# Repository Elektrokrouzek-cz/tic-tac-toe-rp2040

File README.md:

# Tic-tac-toe based on RP2040
This is the construction of tic-tac-toe game based on Raspberry Pi Pico (RP2040). It consists of 3x3 game layout with Neopixel 5mm LEDs and buttons.

Code is written in Micropython

PCB is 2-layer and was designed using KiCad 9. Fabrication output for JLCPCB is in gerber folder.

**Happy coldering and coding**

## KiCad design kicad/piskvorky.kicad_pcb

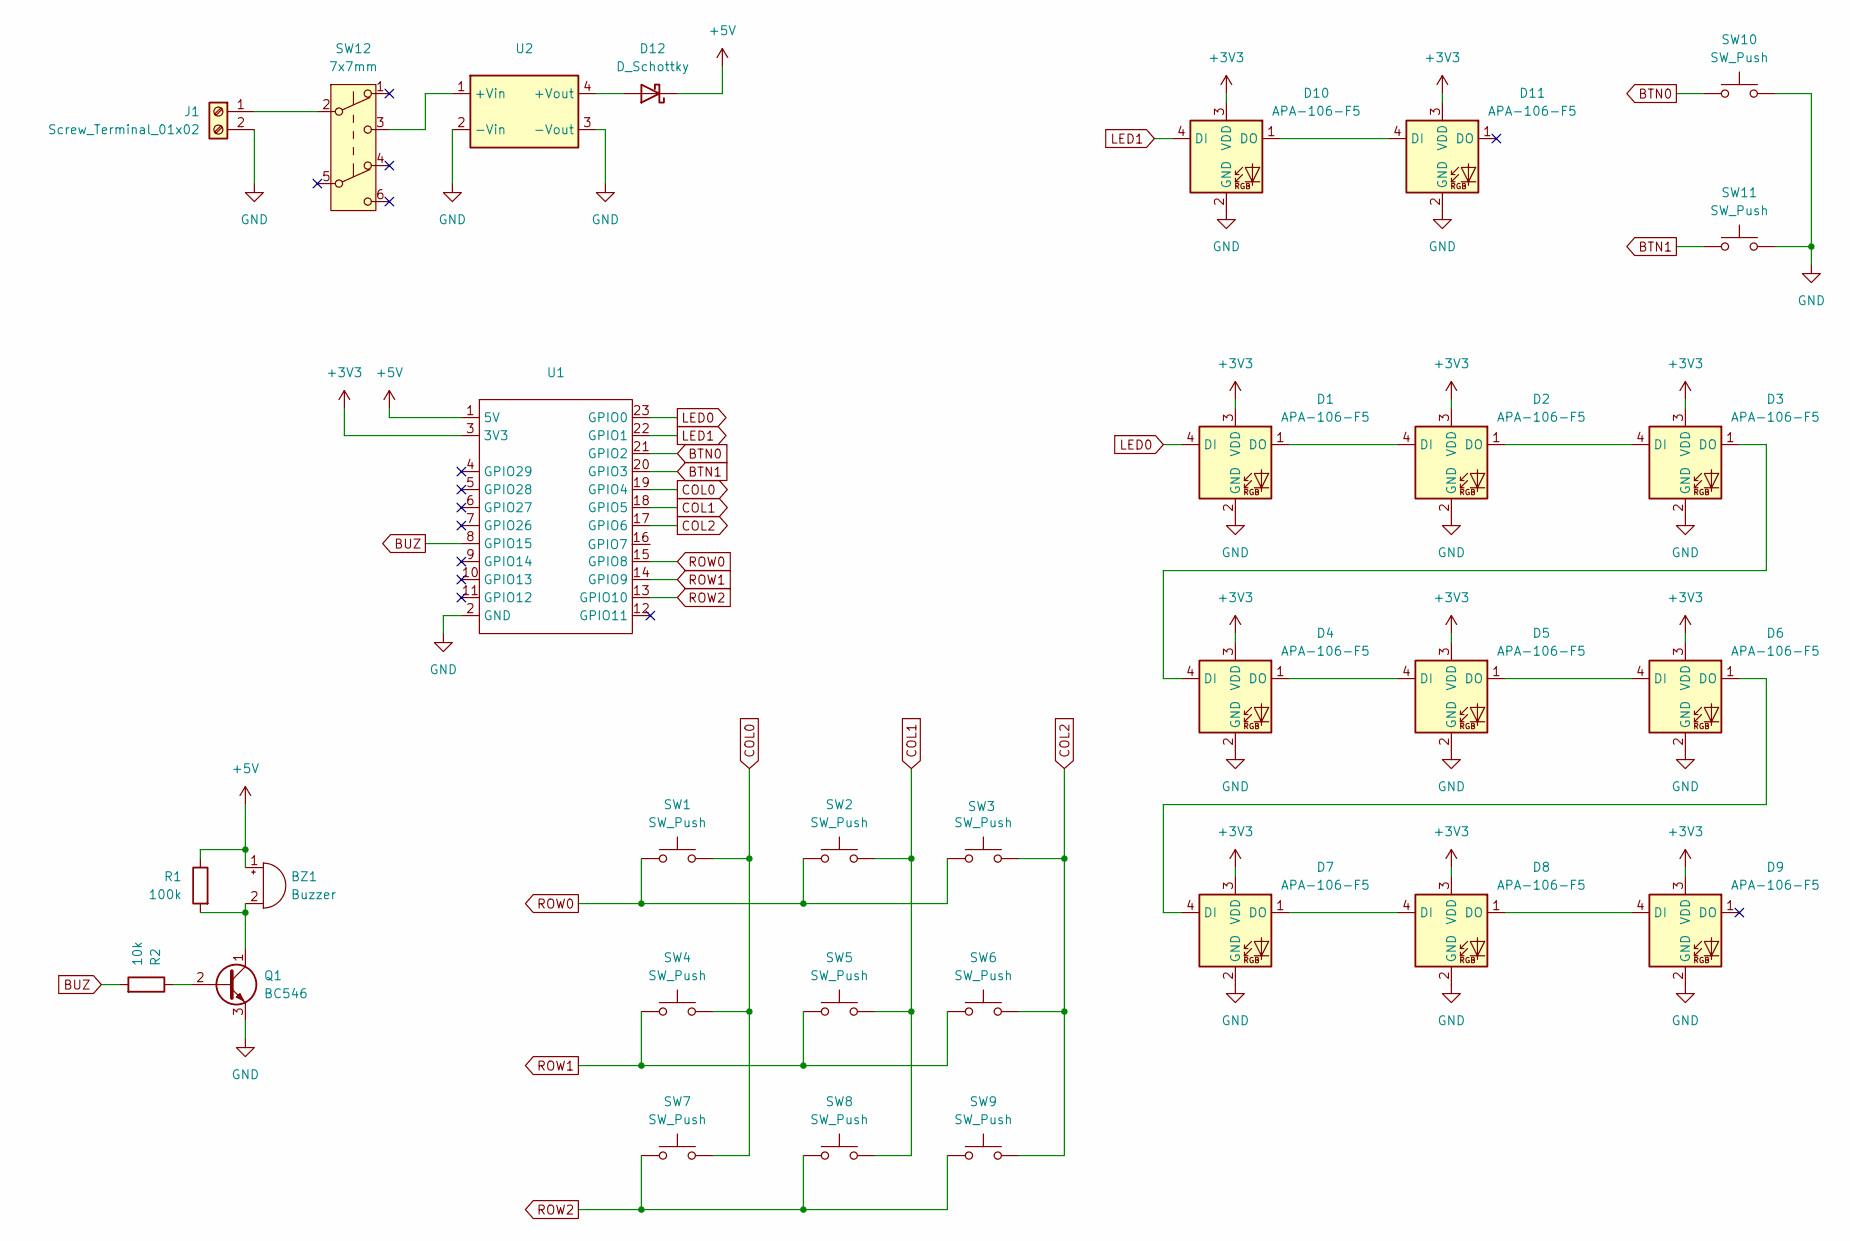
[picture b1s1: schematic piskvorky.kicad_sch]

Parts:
BZ1: Buzzer; Buzzer_12x9.5RM7.6
D1, D2, D3, D4, D5, D6, D7, D8, D9, D10, D11: APA-106-F5; LED_D5.0mm-4_RGB
D12: D_Schottky; D_DO-35_SOD27_P7.62mm_Horizontal
J1: Screw_Terminal_01x02; TerminalBlock_4Ucon_1x02_P3.50mm_Horizontal
Q1: BC546; TO-92_Inline_Wide
R1: 100k; R_Axial_DIN0207_L6.3mm_D2.5mm_P7.62mm_Horizontal
R2: 10k; R_Axial_DIN0207_L6.3mm_D2.5mm_P7.62mm_Horizontal
SW1, SW2, SW3, SW4, SW5, SW6, SW7, SW8, SW9, SW10, SW11: SW_Push; SW_PUSH_6mm_H5mm
SW12: 7x7mm; SW_DPDT_7x7_Turbo
U1: Waveshare RP2040
U2: DC-DC-18x12mm

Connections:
+3V3: D1.3 (VDD), D2.3 (VDD), D3.3 (VDD), D4.3 (VDD), D5.3 (VDD), D6.3 (VDD), D7.3 (VDD), D8.3 (VDD), D9.3 (VDD), D10.3 (VDD), D11.3 (VDD), U1.3 (3V3)
+5V: BZ1.1 (+), D12.1 (K), R1.1, U1.1 (5V)
BTN0: SW10.1, U1.21 (GPIO2)
BTN1: SW11.1, U1.20 (GPIO3)
BUZ: R2.2, U1.8 (GPIO15)
COL0: SW1.2, SW4.2, SW7.2, U1.19 (GPIO4)
COL1: SW2.2, SW5.2, SW8.2, U1.18 (GPIO5)
COL2: SW3.2, SW6.2, SW9.2, U1.17 (GPIO6)
GND: D1.2 (GND), D2.2 (GND), D3.2 (GND), D4.2 (GND), D5.2 (GND), D6.2 (GND), D7.2 (GND), D8.2 (GND), D9.2 (GND), D10.2 (GND), D11.2 (GND), J1.2, Q1.3 (E), SW10.2, SW11.2, U1.2 (GND), U2.2 (-Vin), U2.3 (-Vout)
LED0: D1.4 (DI), U1.23 (GPIO0)
LED1: D10.4 (DI), U1.22 (GPIO1)
unnamed: BZ1.2 (-), Q1.1 (C), R1.2
unnamed: D1.1 (DO), D2.4 (DI)
unnamed: D2.1 (DO), D3.4 (DI)
unnamed: D3.1 (DO), D4.4 (DI)
unnamed: D4.1 (DO), D5.4 (DI)
unnamed: D5.1 (DO), D6.4 (DI)
unnamed: D6.1 (DO), D7.4 (DI)
unnamed: D7.1 (DO), D8.4 (DI)
unnamed: D8.1 (DO), D9.4 (DI)
unnamed: D10.1 (DO), D11.4 (DI)
unnamed: D12.2 (A), U2.4 (+Vout)
unnamed: J1.1, SW12.2 (B)
unnamed: Q1.2 (B), R2.1
unnamed: SW12.3 (C), U2.1 (+Vin)
ROW0: SW1.1, SW2.1, SW3.1, U1.15 (GPIO8)
ROW1: SW4.1, SW5.1, SW6.1, U1.14 (GPIO9)
ROW2: SW7.1, SW8.1, SW9.1, U1.13 (GPIO10)

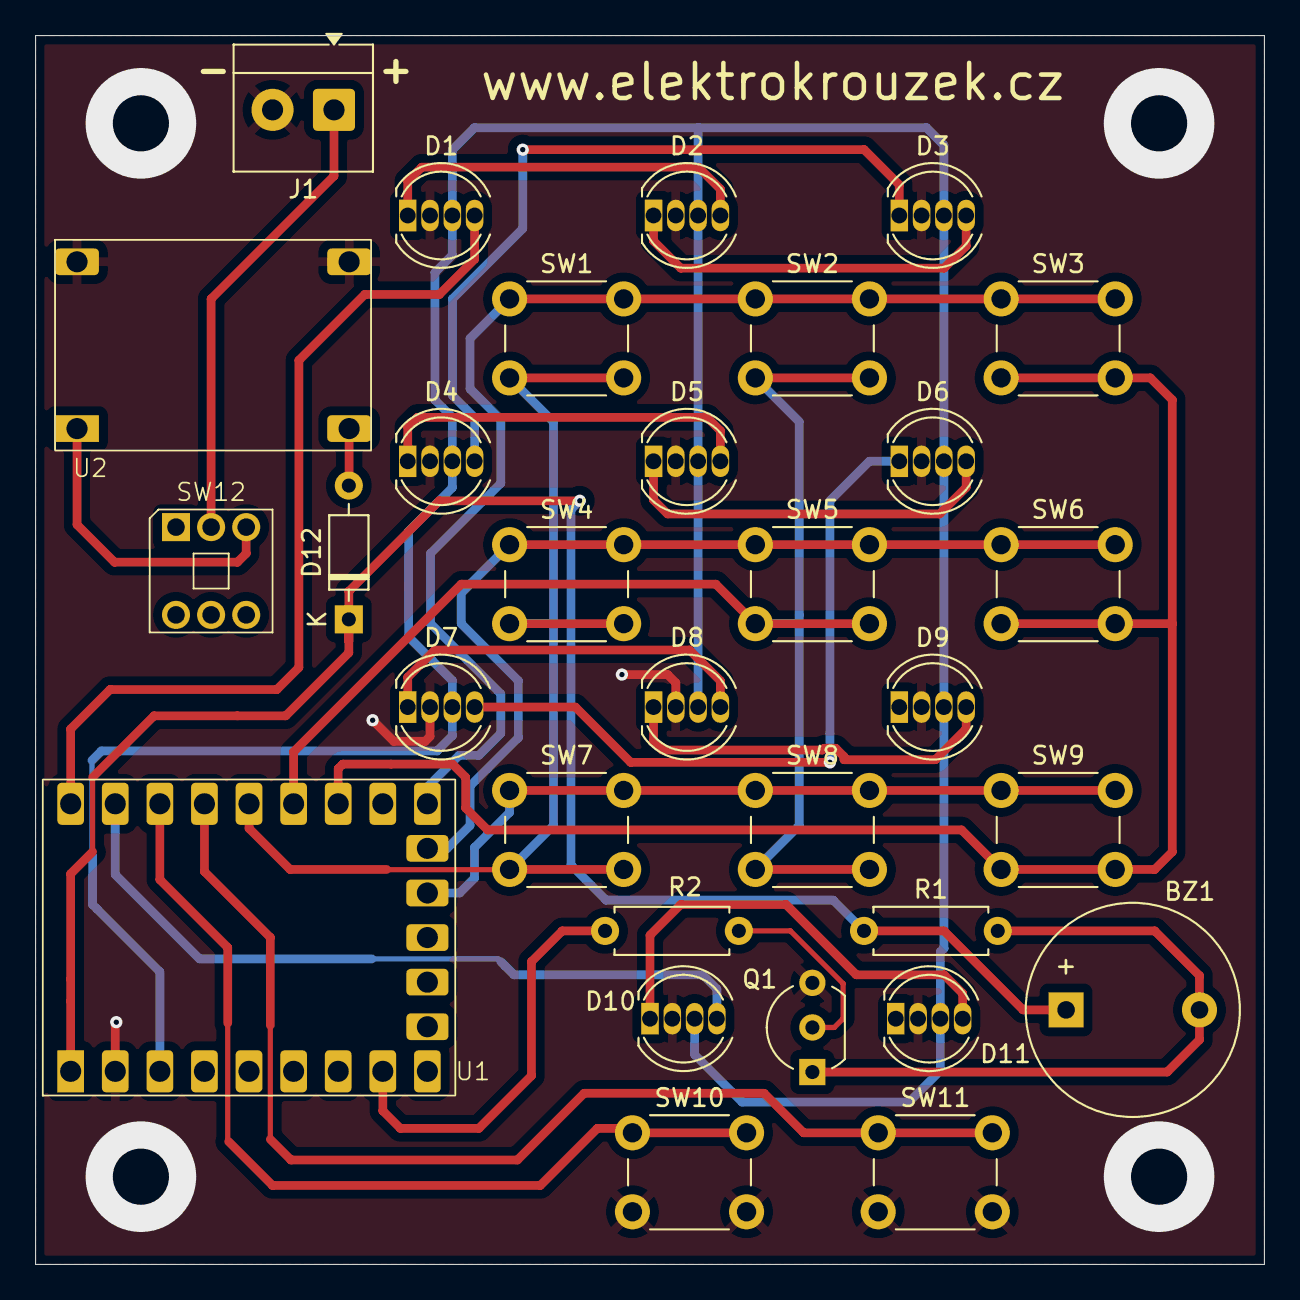
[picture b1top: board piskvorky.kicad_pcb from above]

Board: 2 copper layers, 70.0 x 70.0 mm, 31 parts (0 on the bottom side), 28 nets.

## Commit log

2025-04-10 Kicad libraries added
2025-06-18 Documentation added
2025-06-18 Readme updated
2025-06-18 Added game photo
